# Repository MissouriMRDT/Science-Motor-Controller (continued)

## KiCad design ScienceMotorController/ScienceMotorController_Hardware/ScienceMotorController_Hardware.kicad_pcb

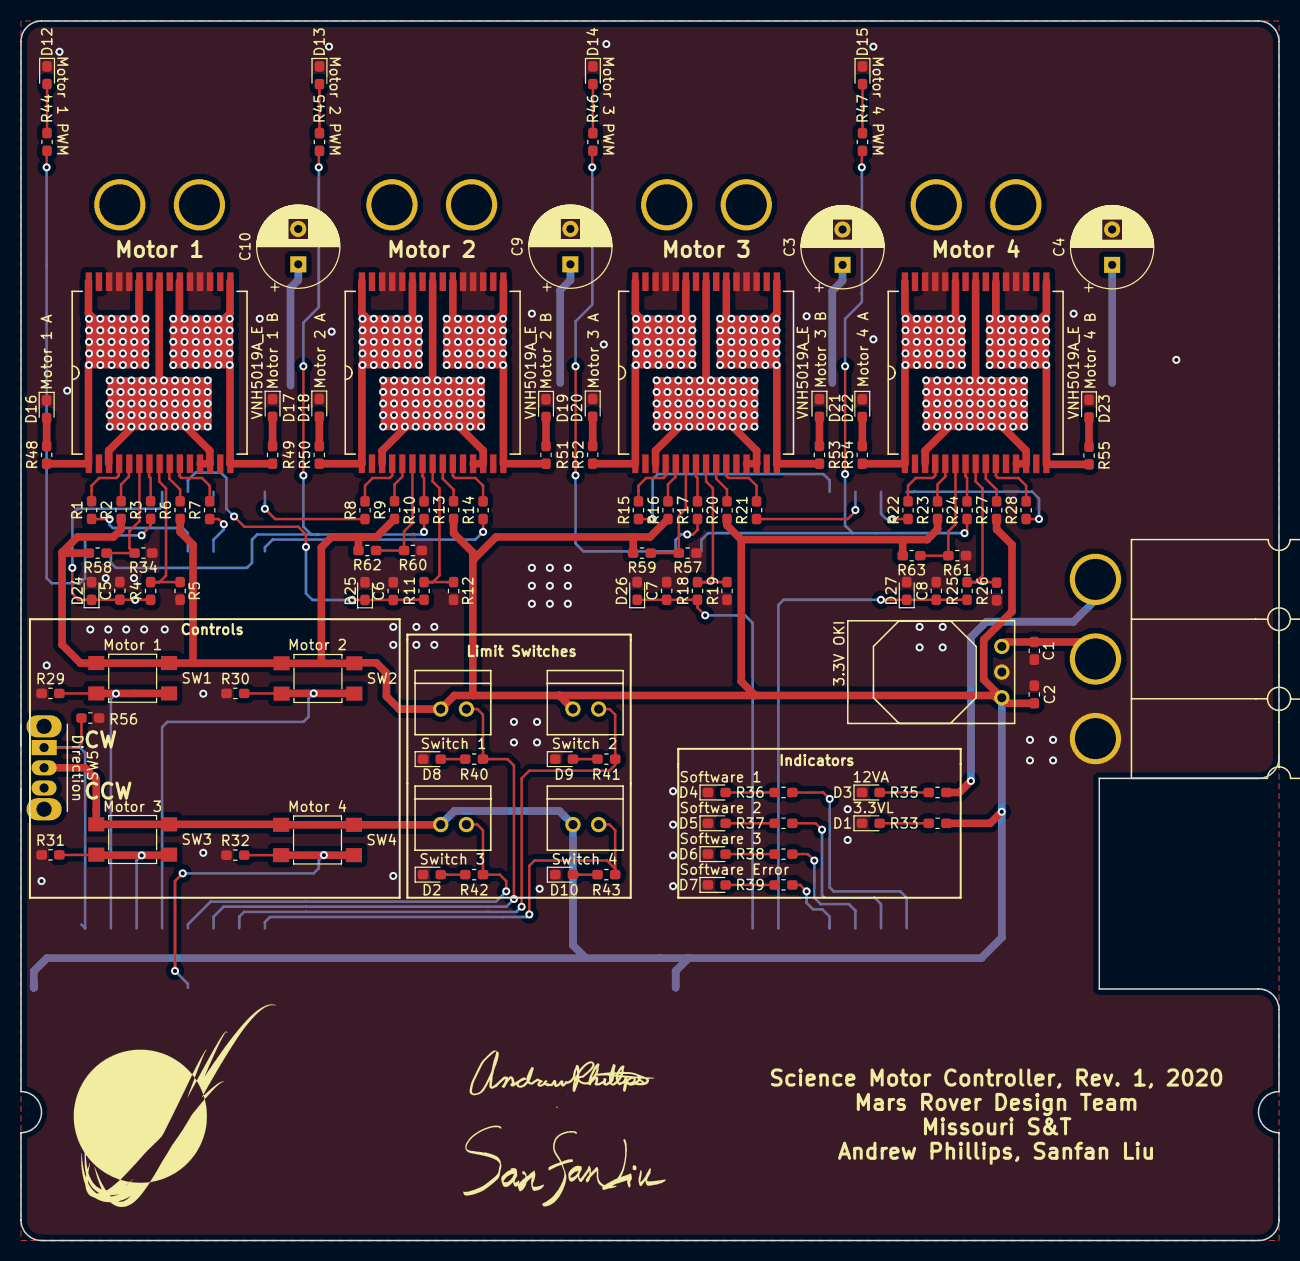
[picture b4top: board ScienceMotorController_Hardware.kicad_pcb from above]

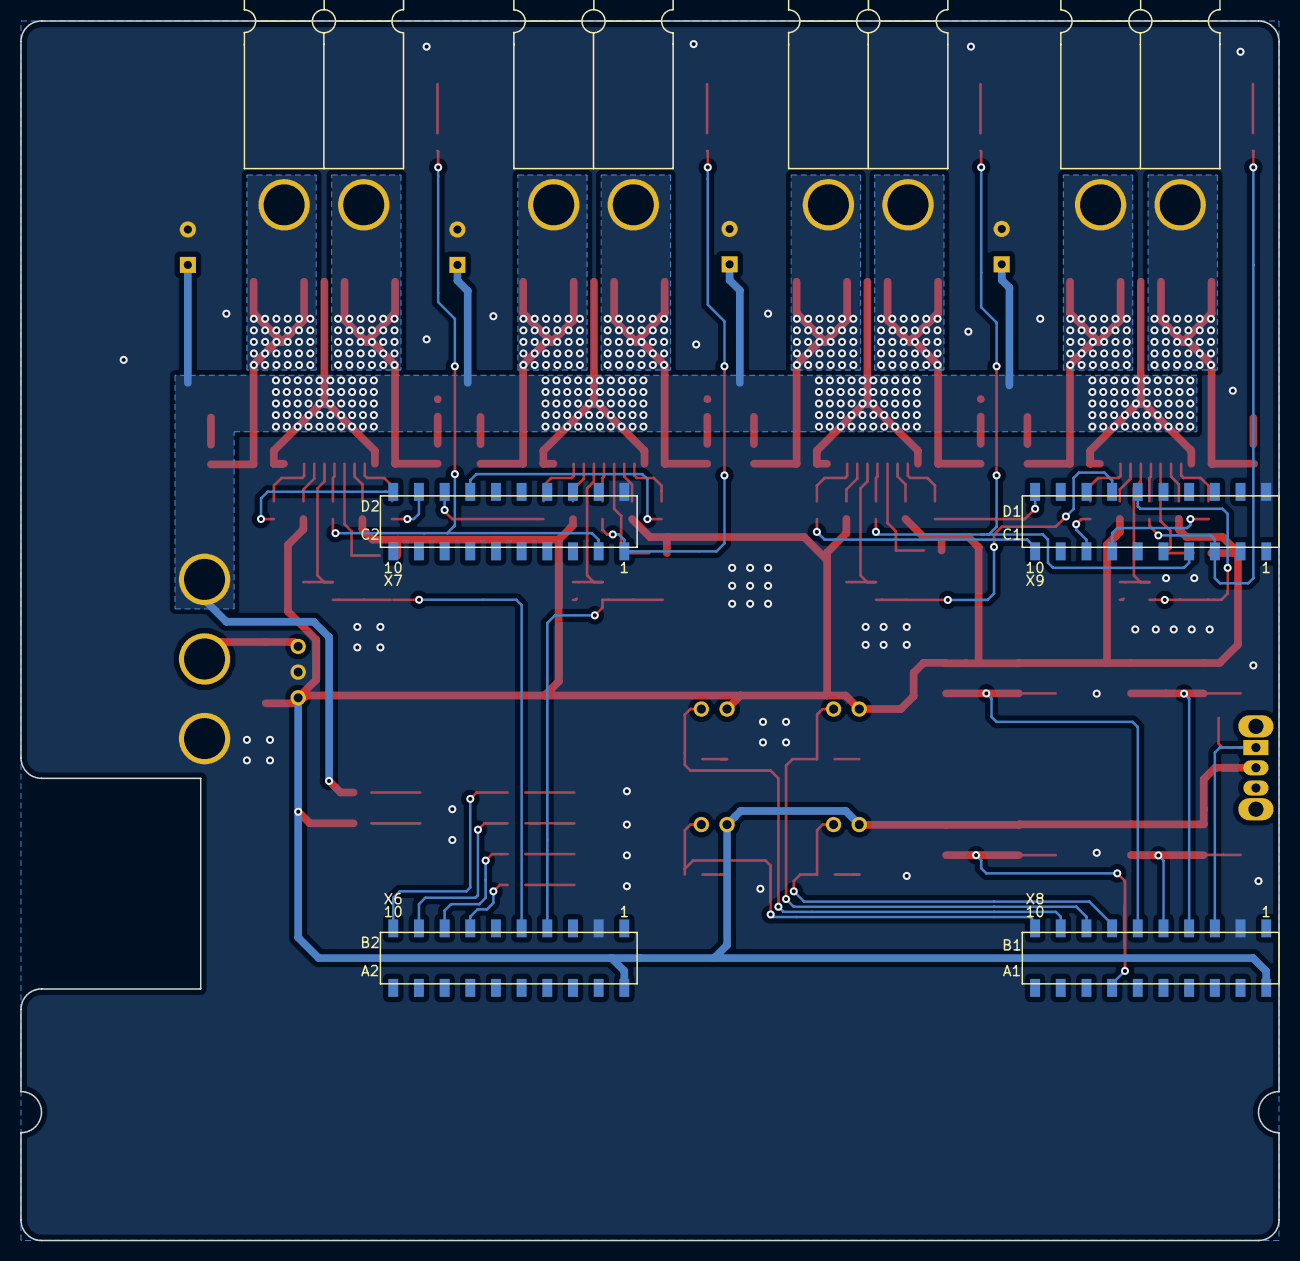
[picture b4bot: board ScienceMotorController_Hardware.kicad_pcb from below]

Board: 2 copper layers, 124.5 x 120.7 mm, 119 parts (4 on the bottom side), 91 nets.

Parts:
C1, C2: 10uF; C_0603_1608Metric_Pad1.05x0.95mm_HandSolder
C3, C4, C9, C10: 470 uF; CP_Radial_D8.0mm_P3.50mm
C5, C6, C7, C8: 33nF; C_0603_1608Metric_Pad1.05x0.95mm_HandSolder
Conn1: AndersonPP; Anderson_3_Horizontal_Side_by_Side
Conn2, Conn3, Conn4, Conn5: AndersonPP; Anderson_2_Horizontal_Side_by_Side
Conn6, Conn7, Conn8, Conn9: Molex_SL_02; MOLEX_SL_02_Vertical
D1: 3.3V_LED; LED_0603_1608Metric_Pad1.05x0.95mm_HandSolder
D2: LS_3_LED; LED_0603_1608Metric_Pad1.05x0.95mm_HandSolder
D3: 12VA_LED; LED_0603_1608Metric_Pad1.05x0.95mm_HandSolder
D4: SW_IND_1_LED; LED_0603_1608Metric_Pad1.05x0.95mm_HandSolder
D5: SW_IND_2_LED; LED_0603_1608Metric_Pad1.05x0.95mm_HandSolder
D6: SW_IND_3_LED; LED_0603_1608Metric_Pad1.05x0.95mm_HandSolder
D7: SW_ERR_LED; LED_0603_1608Metric_Pad1.05x0.95mm_HandSolder
D8: LS_1_LED; LED_0603_1608Metric_Pad1.05x0.95mm_HandSolder
D9: LS_2_LED; LED_0603_1608Metric_Pad1.05x0.95mm_HandSolder
D10: LS_4_LED; LED_0603_1608Metric_Pad1.05x0.95mm_HandSolder
D12: M1_PWM_LED; LED_0603_1608Metric_Pad1.05x0.95mm_HandSolder
D13: M2_PWM_LED; LED_0603_1608Metric_Pad1.05x0.95mm_HandSolder
D14: M3_PWM_LED; LED_0603_1608Metric_Pad1.05x0.95mm_HandSolder
D15: M4_PWM_LED; LED_0603_1608Metric_Pad1.05x0.95mm_HandSolder
D16: M1_OUT_A_LED; LED_0603_1608Metric_Pad1.05x0.95mm_HandSolder
D17: M1_OUT_B_LED; LED_0603_1608Metric_Pad1.05x0.95mm_HandSolder
D18: M2_OUT_A_LED; LED_0603_1608Metric_Pad1.05x0.95mm_HandSolder
D19: M2_OUT_B_LED; LED_0603_1608Metric_Pad1.05x0.95mm_HandSolder
D20: M3_OUT_A_LED; LED_0603_1608Metric_Pad1.05x0.95mm_HandSolder
D21: M3_OUT_B_LED; LED_0603_1608Metric_Pad1.05x0.95mm_HandSolder
D22: M4_OUT_A_LED; LED_0603_1608Metric_Pad1.05x0.95mm_HandSolder
D23: M4_OUT_B_LED; LED_0603_1608Metric_Pad1.05x0.95mm_HandSolder
D24, D25, D26, D27: 3.3 Zener; D_0603_1608Metric_Pad1.05x0.95mm_HandSolder
R1, R2, R3, R6, R7, R8, R9, R10, R13, R14, R15, R16, R17, R20, R21, R22, R23, R24, R27, R28, R48, R49, R50, R51, R52, R53, R54, R55: 1K; R_0603_1608Metric_Pad1.05x0.95mm_HandSolder
R4, R11, R18, R25, R29, R30, R31, R32, R56: 10K; R_0603_1608Metric_Pad1.05x0.95mm_HandSolder
R5, R12, R19, R26, R35: 1.5K; R_0603_1608Metric_Pad1.05x0.95mm_HandSolder
R33: 500; R_0603_1608Metric_Pad1.05x0.95mm_HandSolder
R34, R57, R58, R59, R60, R61, R62, R63: 0; R_0603_1608Metric_Pad1.05x0.95mm_HandSolder
R36, R37, R38, R39, R40, R41, R42, R43, R44, R45, R46, R47: 330; R_0603_1608Metric_Pad1.05x0.95mm_HandSolder
SW1, SW2, SW3, SW4: SW_Push; SW_SPST_TL3305A
SW5: SW_SPDT; SW_CuK_OS102011MA1QN1_SPDT_Angled
U1: TM4C129E_Launchpad; TM4C129E_Launchpad_FULL_SMD_BOTTOM
U2: 3.3V OKI; OKI_Horizontal
U4, U5, U6, U7: VNH5019A_E; MultiPowerSO_30

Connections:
+3V3: C2.1, Conn6.1, Conn7.1, Conn8.1, Conn9.1, R2.1, R6.1, R9.1, R13.1, R16.1, R20.1, R23.1, R27.1, R33.1, R58.2, R59.2, R62.2, R63.2, SW1.1, SW2.1, SW3.1, SW4.1, SW5.2, U1.+3V3, U1.+3V3', U2.3
+12L: C1.1, Conn1.2, U2.1
+12VA: C3.1, C4.1, C9.1, C10.1, Conn1.3, R35.1, U4.3, U4.12, U4.13, U4.23, U4.32, U5.3, U5.12, U5.13, U5.23, U5.32, U6.3, U6.12, U6.13, U6.23, U6.32, U7.3, U7.12, U7.13, U7.23, U7.32
GND: C1.2, C2.2, C3.2, C4.2, C5.2, C6.2, C7.2, C8.2, C9.2, C10.2, Conn1.1, D1.1, D2.1, D3.1, D4.1, D5.1, D6.1, D7.1, D8.1, D9.1, D10.1, D12.1, D13.1, D14.1, D15.1, D16.1, D17.1, D18.1, D19.1, D20.1, D21.1, D22.1, D23.1, D24.2, D25.2, D26.2, D27.2, R5.2, R12.2, R19.2, R26.2, R29.1, R30.1, R31.1, R32.1, R34.1, R56.1, R57.1, R60.1, R61.1, U1.GND, U2.2, U4.18, U4.19, U4.20, U4.26, U4.27, U4.28, U5.18, U5.19, U5.20, U5.26, U5.27, U5.28, U6.18, U6.19, U6.20, U6.26, U6.27, U6.28, U7.18, U7.19, U7.20, U7.26, U7.27, U7.28
LS_1: Conn6.2, R40.1, U1.PA6
LS_2: Conn7.2, R41.1, U1.PM4
LS_3: Conn8.2, R42.1, U1.PD7
LS_4: Conn9.2, R43.1, U1.PM5
M1_CS: C5.1, D24.1, R4.1, U1.PD1
M1_IN_A: R1.1, U1.PL0
M1_IN_B: R7.1, U1.PL1
M1_OUT_A: Conn2.1, R48.1, U4.1, U4.25, U4.30, U4.31
M1_OUT_B: Conn2.2, R49.1, U4.15, U4.16, U4.21, U4.33
M1_PWM: R3.1, R44.2, U1.PF3
M2_CS: C6.1, D25.1, R11.1, U1.PD0
M2_IN_A: R8.1, U1.PP2
M2_IN_B: R14.1, U1.PL3
M2_OUT_A: Conn3.1, R50.1, U5.1, U5.25, U5.30, U5.31
M2_OUT_B: Conn3.2, R51.1, U5.15, U5.16, U5.21, U5.33
M2_PWM: R10.1, R45.2, U1.PG0
M3_CS: C7.1, D26.1, R18.1, U1.PB5
M3_IN_A: R15.1, U1.PQ3
M3_IN_B: R21.1, U1.PP3
M3_OUT_A: Conn4.1, R52.1, U6.1, U6.25, U6.30, U6.31
M3_OUT_B: Conn4.2, R53.1, U6.15, U6.16, U6.21, U6.33
M3_PWM: R17.1, R46.2, U1.PG1
M4_CS: C8.1, D27.1, R25.1, U1.PK0
M4_IN_A: R22.1, U1.PQ1
M4_IN_B: R28.1, U1.PM6
M4_OUT_A: Conn5.1, R54.1, U7.1, U7.25, U7.30, U7.31
M4_OUT_B: Conn5.2, R55.1, U7.15, U7.16, U7.21, U7.33
M4_PWM: R24.1, R47.2, U1.PK4
MSW_1: R29.2, SW1.2, U1.PE1
MSW_2: R30.2, SW2.2, U1.PE3
MSW_3: R31.2, SW3.2, U1.PE2
MSW_4: R32.2, SW4.2, U1.PD3
MSW_5: R56.2, SW5.1, U1.PE0
unnamed: D1.2, R33.2
unnamed: D2.2, R42.2
unnamed: D3.2, R35.2
unnamed: D4.2, R36.2
unnamed: D5.2, R37.2
unnamed: D6.2, R38.2
unnamed: D7.2, R39.2
unnamed: D8.2, R40.2
unnamed: D9.2, R41.2
unnamed: D10.2, R43.2
unnamed: D12.2, R44.1
unnamed: D13.2, R45.1
unnamed: D14.2, R46.1
unnamed: D15.2, R47.1
unnamed: D16.2, R48.2
unnamed: D17.2, R49.2
unnamed: D18.2, R50.2
unnamed: D19.2, R51.2
unnamed: D20.2, R52.2
unnamed: D21.2, R53.2
unnamed: D22.2, R54.2
unnamed: D23.2, R55.2
unnamed: R1.2, U4.4
unnamed: R2.2, U4.5
unnamed: R3.2, U4.7
unnamed: R4.2, R5.1, U4.8
unnamed: R6.2, U4.9
unnamed: R7.2, U4.10
unnamed: R8.2, U5.4
unnamed: R9.2, U5.5
unnamed: R10.2, U5.7
unnamed: R11.2, R12.1, U5.8
unnamed: R13.2, U5.9
unnamed: R14.2, U5.10
unnamed: R15.2, U6.4
unnamed: R16.2, U6.5
unnamed: R17.2, U6.7
unnamed: R18.2, R19.1, U6.8
unnamed: R20.2, U6.9
unnamed: R21.2, U6.10
unnamed: R22.2, U7.4
unnamed: R23.2, U7.5
unnamed: R24.2, U7.7
unnamed: R25.2, R26.1, U7.8
unnamed: R27.2, U7.9
unnamed: R28.2, U7.10
unnamed: R34.2, R58.1, U4.6
unnamed: R57.2, R59.1, U6.6
unnamed: R60.2, R62.1, U5.6
unnamed: R61.2, R63.1, U7.6
SW_ERR: R39.1, U1.PK2
SW_IND_1: R36.1, U1.PA5
SW_IND_2: R37.1, U1.PA4
SW_IND_3: R38.1, U1.PK3

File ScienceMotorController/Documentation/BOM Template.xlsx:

Id | Designator | Package | Quantity | Designation | Item Name | Part Number | Vendor | Cost Per Item | Cost | URL | Comments
1 | U5,U4,U6,U7 | MultiPowerSO_30 | 4 | VNH5019A_E | VNH5019ATR-E | 497-13073-1-ND | Digikey | 7.91 | 31.64 | https://www.digikey.com/product-detail/en/stmicroelectronics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 |  |  |  | Total Cost
2 | R43,R39,R40,R41,R44,R45,R46,R47,R42 | R_0603_1608Metric_Pad1.05x0.95mm_HandSolder | 9 | 330 | CRCW0603330RJNEA | 59M6805 | Newark | 2E-3 | 1.8000000000000002E-2 | https://www.newark.com/vishay/crcw0603330rjnea/res-thick-fil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 |  |  |  | 19.779
3 | R36,R37,R38,R29,R30,R31,R32,R33,R56 | R_0603_1608Metric_Pad1.05x0.95mm_HandSolder | 9 | 500 | CRCW0603510RJNEA | 59M6823 | Newark | 4.0000000000000001E-3 | 3.6000000000000004E-2 | https://www.newark.com/vishay/crcw0603510rjnea/res-thick-fil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
4 | C8,C5,C6,C7 | C_0603_1608Metric_Pad1.05x0.95mm_HandSolder | 4 | 33nF | 311-4001-1 | 311-4001-1-ND | Digikey | 0.11 | 0.44 | https://www.digikey.com/product-detail/en/yageo/CC0603JRX7R8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
5 | C1,C2 | C_0603_1608Metric_Pad1.05x0.95mm_HandSolder | 2 | 10uF | 1608-1357-1 | 1608-1357-1-ND | Digikey | 0.35 | 0.7 | https://www.digikey.com/product-detail/en/knowles-syfer/0603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
6 | Conn1 | Anderson_3_Horizontal_Side_by_Side | 1 | AndersonPP |  |  |  |  | 0
7 | Conn2,Conn3,Conn4,Conn5 | Anderson_2_Horizontal_Side_by_Side | 4 | AndersonPP |  |  |  |  | 0
8 | D1 | LED_0603_1608Metric_Pad1.05x0.95mm_HandSolder | 1 | 3.3V_LED | SML-LX0603GW-TR | 75K1440 | Newark | 0.24299999999999999 | 0.24299999999999999 | https://www.newark.com/lumex/sml-lx0603gw-tr/led-green-0-8mm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
9 | D3 | LED_0603_1608Metric_Pad1.05x0.95mm_HandSolder | 1 | 12VA_LED | SML-LX0603GW-TR | 75K1440 | Newark | 0.24299999999999999 | 0.24299999999999999 | https://www.newark.com/lumex/sml-lx0603gw-tr/led-green-0-8mm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
10 | D4 | LED_0603_1608Metric_Pad1.05x0.95mm_HandSolder | 1 | SW_IND_1_LED | SML-LX0603USBW-TR | 70M9169 | Newark | 1.03 | 1.03 | https://www.newark.com/lumex/sml-lx0603usbw-tr/led-blue-0-8m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
11 | D5 | LED_0603_1608Metric_Pad1.05x0.95mm_HandSolder | 1 | SW_IND_2_LED | SML-LX0603USBW-TR | 70M9169 | Newark | 1.03 | 1.03 | https://www.newark.com/lumex/sml-lx0603usbw-tr/led-blue-0-8m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
12 | D6 | LED_0603_1608Metric_Pad1.05x0.95mm_HandSolder | 1 | SW_IND_3_LED | SML-LX0603USBW-TR | 70M9169 | Newark | 1.03 | 1.03 | https://www.newark.com/lumex/sml-lx0603usbw-tr/led-blue-0-8m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
13 | D7 | LED_0603_1608Metric_Pad1.05x0.95mm_HandSolder | 1 | SW_ERR_LED | SML-LX0603SIW-TR | 09J9435 | Newark | 0.62 | 0.62 | https://www.newark.com/lumex/sml-lx0603siw-tr/led-red-0-8mm-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
14 | D8 | LED_0603_1608Metric_Pad1.05x0.95mm_HandSolder | 1 | LS_1_LED | SML-LX0603SYW-TR | 28M9280 | Newark | 0.107 | 0.107 | https://www.newark.com/lumex/sml-lx0603syw-tr/led-yellow-0-8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
15 | D9 | LED_0603_1608Metric_Pad1.05x0.95mm_HandSolder | 1 | LS_2_LED | SML-LX0603SYW-TR | 28M9280 | Newark | 0.107 | 0.107 | https://www.newark.com/lumex/sml-lx0603syw-tr/led-yellow-0-8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
14 | D2 | LED_0603_1608Metric_Pad1.05x0.95mm_HandSolder | 1 | LS_1_LED | SML-LX0603SYW-TR | 28M9280 | Newark | 0.107 | 0.107 | https://www.newark.com/lumex/sml-lx0603syw-tr/led-yellow-0-8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
15 | D10 | LED_0603_1608Metric_Pad1.05x0.95mm_HandSolder | 1 | LS_2_LED | SML-LX0603SYW-TR | 28M9280 | Newark | 0.107 | 0.107 | https://www.newark.com/lumex/sml-lx0603syw-tr/led-yellow-0-8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
16 | D12 | LED_0603_1608Metric_Pad1.05x0.95mm_HandSolder | 1 | M1_PWM_LED | SML-LX0603SYW-TR | 28M9280 | Newark | 0.107 | 0.107 | https://www.newark.com/lumex/sml-lx0603syw-tr/led-yellow-0-8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
17 | D13 | LED_0603_1608Metric_Pad1.05x0.95mm_HandSolder | 1 | M2_PWM_LED | SML-LX0603SYW-TR | 28M9280 | Newark | 0.107 | 0.107 | https://www.newark.com/lumex/sml-lx0603syw-tr/led-yellow-0-8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
18 | D14 | LED_0603_1608Metric_Pad1.05x0.95mm_HandSolder | 1 | M3_PWM_LED | SML-LX0603SYW-TR | 28M9280 | Newark | 0.107 | 0.107 | https://www.newark.com/lumex/sml-lx0603syw-tr/led-yellow-0-8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
19 | D15 | LED_0603_1608Metric_Pad1.05x0.95mm_HandSolder | 1 | M4_PWM_LED | SML-LX0603SYW-TR | 28M9280 | Newark | 0.107 | 0.107 | https://www.newark.com/lumex/sml-lx0603syw-tr/led-yellow-0-8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
20 | D16 | LED_0603_1608Metric_Pad1.05x0.95mm_HandSolder | 1 | M1_OUT_A_LED | SML-LX0603SOW-TR | 28M9279 | Newark | 0.11700000000000001 | 0.11700000000000001 | https://www.newark.com/lumex/sml-lx0603sow-tr/led-orange-0-8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
21 | D17 | LED_0603_1608Metric_Pad1.05x0.95mm_HandSolder | 1 | M1_OUT_B_LED | SML-LX0603SOW-TR | 28M9279 | Newark | 0.11700000000000001 | 0.11700000000000001 | https://www.newark.com/lumex/sml-lx0603sow-tr/led-orange-0-8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
22 | D18 | LED_0603_1608Metric_Pad1.05x0.95mm_HandSolder | 1 | M2_OUT_A_LED | SML-LX0603SOW-TR | 28M9279 | Newark | 0.11700000000000001 | 0.11700000000000001 | https://www.newark.com/lumex/sml-lx0603sow-tr/led-orange-0-8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
23 | D19 | LED_0603_1608Metric_Pad1.05x0.95mm_HandSolder | 1 | M2_OUT_B_LED | SML-LX0603SOW-TR | 28M9279 | Newark | 0.11700000000000001 | 0.11700000000000001 | https://www.newark.com/lumex/sml-lx0603sow-tr/led-orange-0-8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
24 | D20 | LED_0603_1608Metric_Pad1.05x0.95mm_HandSolder | 1 | M3_OUT_A_LED | SML-LX0603SOW-TR | 28M9279 | Newark | 0.11700000000000001 | 0.11700000000000001 | https://www.newark.com/lumex/sml-lx0603sow-tr/led-orange-0-8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
25 | D21 | LED_0603_1608Metric_Pad1.05x0.95mm_HandSolder | 1 | M3_OUT_B_LED | SML-LX0603SOW-TR | 28M9279 | Newark | 0.11700000000000001 | 0.11700000000000001 | https://www.newark.com/lumex/sml-lx0603sow-tr/led-orange-0-8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
26 | D22 | LED_0603_1608Metric_Pad1.05x0.95mm_HandSolder | 1 | M4_OUT_A_LED | SML-LX0603SOW-TR | 28M9279 | Newark | 0.11700000000000001 | 0.11700000000000001 | https://www.newark.com/lumex/sml-lx0603sow-tr/led-orange-0-8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
27 | D23 | LED_0603_1608Metric_Pad1.05x0.95mm_HandSolder | 1 | M4_OUT_B_LED | SML-LX0603SOW-TR | 28M9279 | Newark | 0.11700000000000001 | 0.11700000000000001 | https://www.newark.com/lumex/sml-lx0603sow-tr/led-orange-0-8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
28 | R1,R2,R3,R6,R7,R8,R9,R10,R13,R14,R15,R16,R17,R20,R21,R22,R23,R24,R27,R28 | R_0603_1608Metric_Pad1.05x0.95mm_HandSolder | 20 | 1K | ESR03EZPJ102 | 59AC6943 | Newark | 0.1 | 2 | https://www.newark.com/rohm/esr03ezpj102/res-1k-5-0603-thick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
29 | R4,R11,R18,R25 | R_0603_1608Metric_Pad1.05x0.95mm_HandSolder | 4 | 10K |  |  |  |  | 0
30 | R5,R12,R19,R26,R35,R48,R49,R50,R51,R52,R53,R54,R55 | R_0603_1608Metric_Pad1.05x0.95mm_HandSolder | 13 | 1.5K |  |  |  |  | 0
31 | SW1,SW2,SW3,SW4 | SW_SPST_TL3305A | 4 | SW_Push |  |  |  |  | 0
32 | U2 | OKI_Horizontal | 1 | 3.3V OKI | OKI-78SR-3 | 58T9850 | Newark | 4.57 | 4.57 | https://www.newark.com/murata-power-solutions/oki-78sr-3-3-1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
33 | Conn8,Conn9,Conn6,Conn7 | MOLEX_SL_02_Vertical | 4 | Molex_SL_02 | 70543-0001 | 59H2645 | Newark | 0.745 | 2.98 | https://www.newark.com/molex/70543-0001/connector-header-2po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
34 | D24,D25,D26,D27 | D_0603_1608Metric_Pad1.05x0.95mm_HandSolder | 4 | 3.3 |  |  |  |  | 0
35 | U1 | TM4C129E_Launchpad_FULL_SMD_BOTTOM | 1 | TM4C129E_Launchpad |  |  |  |  | 0
36 | C3,C4,C9,C10 | CP_Radial_D8.0mm_P3.50mm | 4 | 470 uF |  |  |  |  | 0
37 | SW5 | SW_CuK_OS102011MA1QN1_SPDT_Angled | 1 | SW_SPDT |  |  |  |  | 0

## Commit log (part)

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2019-10-05 Started Schematic
2019-10-08 Added Indicators and Pins
2019-10-08 Controls Added and Schematic Organized
2019-10-08 Updated Schematic Labels and Organization
2019-10-08 (Most) Footprints Assigned
2019-10-08 Footprints and Pins Finished Schematic
2019-10-10 Basic board organization
2019-10-11 Went Overboard on Traces
2019-10-11 Almost All Traces, Ground and 3V3 Polygons
2019-10-12 Finally Added Silkscreens
2019-10-12 Routed All Traces
2019-10-12 Fixed Silkscreen
2019-10-13 PDR Advice
    Removed 2 limit switches & relocated LS LEDs, added direction switch. Also relocated LS, Control, and Indicator blocks and revamped pin assignments to optimize traces.
2019-10-13 Finished Traces
2019-11-16 Added Pin Mapping
2019-12-13 Moving to Rev1 PRR
2019-12-13 Updated Directory Format
2019-12-13 PRR Complete
2019-12-14 BOM Finished
2019-12-14 Step files, updated pin layout, cleaned schematic
2020-09-12 New Repo
2020-09-25 Added Power Sheet
2020-09-25 Added 3.3v buck, created tiva hierachal sheet
2020-09-25 Placed Tiva headers, took note of which pins were PWM
2020-09-25 Added 12VA anderson
2020-10-05 power indicators
2020-10-05 created motors hierarchal sheet, added VNH IC
2020-10-07 Set up VNH IC's
2020-10-07 limit switch indicators
2020-10-07 Flagged Tiva
2020-10-09 changed everything to actuation, added schottky diode, added A/B flags to tiva
2020-10-10 added ferrite beads
2020-10-16 schematic review
2020-10-16 made some more hierarchal changes
2020-10-28 fixed hierarchical
2020-10-31 Fixed 3.3V, added encoders
2020-11-10 added logic line
2020-11-12 annotated
2020-11-12 assigned most of the footprints
2020-11-12 finished assigning footprints, generated pcbnew
2020-11-13 began placing footprints on layout
2020-11-13 more component placing, added ground plane
2020-11-14 added traces for first vnh
2020-11-14 layout work
2020-11-14 more layout work
2020-11-15 finished arranging components
2020-11-15 running traces
2020-11-15 routed more traces
2020-11-15 finished routing traces
2020-11-25 added oki and began rerouting traces
2020-11-26 rerouted traces
2020-11-26 added silkscreens
2020-11-26 added bom
2020-11-26 Added Gerbs
2020-11-26 created step files
2020-11-30 cleaned up vias, widened planes, grounded more areas
2020-12-02 fixed that one trace
2020-12-02 one stray trace
2020-12-02 Fixed Gerbs and Step files
2020-12-02 Fixed BOM mistakes
2021-10-10 schematic meeting review
2021-10-10 Created Branch
2021-11-01 Schematic changes: Added 5V converter and Servos
    Schematic:
    -Added a 5V converter to the power section, connected to Power
    -Added Servos in their own section, altered TIVA to add servo connections
2021-11-30 Finished Schematic
    -Changed Motor Controller Chips
    -Removed 2 Pumps
    -Removed 2 Limit Switches
    -Added 2 Absolute Encoders
    -Added 3 Solenoid Valves
    -Created Schematic Symbol and Footprint for Mosfet (footprint may need to be altered later)
2021-11-30 Netlist Generated
    Generated the netlist for the schematic
2021-12-02 Updated Power
2021-12-02 Added Clock Circuit
2021-12-02 Created PCB and Put Close Components Near Each other
2021-12-03 Edge cuts, GND plane, a little more organized
2021-12-04 Worked on patterns for SolValve, LimSwitch, OKIs, and Clock for PCB
2021-12-04 Added 4 More Limit Switches
2021-12-04 Reassigned Encoder Pins
2021-12-04 Put New LimSwitch compoments next to eachother in PCB layout
2021-12-04 Bunch more traces, slightly fixed some schematic issues
    - LEDs on the solenoid valves were incorrectly labeled as "green".
    - The front plane of the board is now +12VA instead of ground
2021-12-04 Put components on the board and added some traces
2021-12-12 added daisy chain ports, updated andersons
2021-12-12 modified: Hardware/ScienceMotorController/ScienceMotorController.kicad_pcb modified: Hardware/ScienceMotorController/ScienceMotorController.kicad_pcb-bak modified: Hardware/ScienceMotorController/Sci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
2021-12-12 created moco circuits
    Use the GND pin 25 on a 5mil grid with the entire circuit selected to move around
2021-12-12 added components to layout
2021-12-12 organized components to be more space efficient
2021-12-13 changed on oki to 5V actuation for servos, began making solenoid circuits
2021-12-13 more connections, components, and plane changes
2021-12-14 connected servo, sw, solenoid traces. more organization
2021-12-14 more connections made, beginning to connect moco ICs
2021-12-14 resistors on moco chips added.
    Had changed netlist to try a different placement for the motor LEDs, but reverted to original position
2021-12-15 finished moco alignment
2021-12-15 connected 5V and osc. buses to moco ICs. Updated netlist to have pins closer to tiva pins
2021-12-15 continued connecting caps and resistors. Moved around some Tiva pins for the moco ICs
2021-12-15 began reworking moco IC control traces. Will need to rearrange the netlist to reduce complexity of traces
2021-12-15 Completed Board and reviewed with Electrical Leadership
2021-12-16 file cleanup
2021-12-16 removed redundant footprint library
2021-12-17 completed board, ready for ordering
2021-12-27 generated gerbs
2021-12-30 began fixing rescue libraries
    created ScienceMotorController.lib as the new project level library
2021-12-30 removed backup files for the rescue library
2021-12-30 removed redundant libraries
2022-02-22 Layout Ready For Review
2022-02-22 Traces Under Mocos
2022-02-22 Changed Ground Plane for Motor Stalls
2022-02-22 Board Review Changes
2022-02-22 9 Solenoids, Fixed PWM Overlap
2022-02-25 Removed 5V Oki, Moved +12V Passthrough Trace, Added Zener Diodes for Current Sense
2022-03-12 ok but actually this time
2022-03-20 Connected Moco Pads, new Gerbs
2022-09-15 Changed motor controllers to H-bridges
2022-09-15 Modified PWM flags
    Modified PWM flags so orientation matched signal direction, also included whole Project along with generated BOM
2022-09-28 Updated H-bridges and LEDs
2022-09-30 Moved LED to motor outputs
2022-09-30 Plot is PDF
2022-10-11 Updated Motor Controllers
    Now has 7 motor controllers. Relabeled flags on MOCOs. Deleted solenoids. Need to add flags to TIVAs.
2022-10-17 Added Servos
2022-10-17 Added Annotations
2022-10-18 Started Layout
    Update H-Bridges. Added Footprints. Started Layout with edge cuts and coopers.
2022-10-19 Started Layout Design
2022-10-25 Organized Layout
2022-10-26 Layout for Encoders, Servos, and Limit Switches
2022-10-29 Attempted an H-Bridge
2022-10-29 Reworked Layout to be better
2022-10-30 Added H-Bridges. Started Traces
2022-10-31 Made traces for servos and encoders
2022-11-02 Rearranged Board. Traced Power and One H-Bridge
2022-11-03 More tracing. Ground is left.
2022-11-03 Finished layout. BOM is left.
2022-11-07 Board Smaller, H-Bridges moved
2022-11-08 Refit Stuff onto Board.
2022-11-09 Added Mounting Holes
2022-11-09 12V plane made. Started Traces.
2022-11-14 Stuff Happened
2022-11-17 Updated to Teensy.
2022-11-17 Added Ethernet. Expanded Board Temporarily
2022-12-10 Updated Schematic and Sorted Footprints
2022-12-18 H-Bridges organized and on board. PCB components sorted.
2022-12-18 Fixed schematic
2022-12-18 Fixed encoder connections
2022-12-19 Organized limit switches
2022-12-19 Wired servo switches
2022-12-19 Finished buttons, servos, and encoders
2022-12-19 Edge cuts + started H Bridges
2022-12-20 Finished H Bridges
2022-12-20 Stitched planes together
2022-12-20 Fixed trace + made STEP file
2022-12-28 Worked on traces
2022-12-28 Finished board
2022-12-28 Generated BOM + Gerbs
2022-12-28 Changed teensy footprint
2022-12-29 Fixed power plane
2023-01-22 remade STEP file
2023-03-08 Schematic created and updated
2023-03-11 Finished schematic and updated footprints
2023-03-13 Layout generated and organized. Still need to draw traces
2023-03-15 H-Bridges made. Rough placement on board done
2023-03-16 H-Bridges traced internally
2023-03-16 Power traces added. Connections within circuits made.
2023-03-16 Traces done. Ground vias left
2023-03-16 Power anderson footprint changed and more GND vias
2023-03-20 Board has been shrunk.
2023-03-20 Added labels
2023-03-20 Moved signature to KiCad libraries
2023-03-20 Made my signature
2023-03-20 Added Signature. Connected capacitor
2023-05-03 Made STEP file
2023-09-06 Removed Outdated files
2023-09-14 Teensy, limit circuit, MOCO
2023-09-19 Added quad encoders, servos, signal
2023-09-22 Boxed all components; edited heater schematic from a 2 pin connector to three pin, including all the previous connections but also adding a 5v supply
2023-09-23 Generated BOM
    Generated and filled out a portion of the BOM (There are two Orange categories currently, since Orange and ORANGE were both listed. Will merge them together next time (Converted the original format t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
2023-09-23 Delete Science_Actuation.csv
    Removed a semi-duplicate Excel file
2023-09-25 Completed BOM
2023-09-26 Fixed Board for Review
    Changed various aspects, such as adding Mounting Holes, replacing 120Ohm resistors for 100Ohm, added footnotes, changed Heater from Comic Sans to default, etc.
2023-09-26 Fixed Remaining things from the schematic review
    Changing schematic size, added flags to Teensy, removed Science Motor Controller
2023-09-28 Changed anderson to logic, edited BOM
2023-10-10 Updated PCB
    Grouped together the various parts of the board
2023-10-12 Updated Science Actuation PCB
    Oriented the board in a better state
2023-10-13 Uploading base template before Traces
    Base template before traces. Still need to change what routes everything will connect to the Teensy
2023-10-15 Added traces and changed the layout of the board
    Some of it is a mess and will probably be revised later
2023-10-18 Temporary state
    Removed things. Added a motor. WIP
2023-10-18 Tried Cleaning Up Board
    Changed layout, added fourth MOCO Breakout
2023-10-19 Added edge cuts
    Added edge cuts
2023-10-19 Fixed mounting hole locations, did ethernet t+/-, still need ground plane
2023-10-21 Updated board
    Made changes to traces, added Conn17 to BOM (Added motor), added MRDT label.
2023-10-21 Added edge cuts and ground plane
2023-10-31 Updated Schematic
    Cleaned up traces and other miscellaneous things
2023-10-31 Fixed errors, edge cuts, gnd planes, and traces
2023-11-05 Updated Rev1 for parts ordering
    Changed 12V and 5V traces, removed servo3, added heater4, updated BOM (may want to doublecheck the BOM), removed SW9, made labels for switches bigger, and hopefully correctly made the GERB
2023-11-09 Final update for Rev1
    Fixed edgecuts, made silkscreen labels cleaner. Regenerated gerb
2024-03-05 Updated Science Actuation schematic (removed some unnecessary components)
2024-03-13 Updating PCB
2024-03-13 Updated Science Actuation again (definitely not finished)
2024-04-02 Updated PCB Board
2024-04-02 Tried making some more changes to the schematic again (resistors, cutting out some unnecessary LEDS, removed connector for MOCOs)
2024-04-04 Fixed alignment, added MOCOs, removed 2 of 7 buttons, remove LEDs on limit switches
2024-04-04 Small alignment changes
2024-04-04 Updated footprints
2024-04-04 Updated PCB components
2024-04-04 Cleaned Schematic, Restarted PCB, Grouped components for each section
2024-04-05 Reposition all components
2024-04-05 Started connecting traces and positioning components of PCB
2024-04-07 Finished schematic and first draft of layout
2024-04-07 Add more caps to VNH and expand 12V plane
2024-04-07 Generate BOM and tune diff pairs
2024-04-07 Generate gerbs
2024-04-08 Reworked Changes to match Arm Mount
    Reworked traces to match Arm mount and proper power plane calculations utilizing empty space
2024-04-08 lots of layout things; got a pretty solid layout for the moco circuits; still needs a decent bit of cleanup, trace routing, via stitching, etc.
2024-04-09 more routing and shtuff
2024-04-09 Review changes and regenerate gerbs
2024-04-09 finishe layout minus labels
2024-04-10 layout finished??
2024-04-10 labels
2024-04-11 Editing BOM
2024-04-11 Updated BoM Spreadsheet
2024-04-11 Add temp and humidity sensors
2024-04-11 Add temp and humidity sensor
2024-04-18 Updated BOM again (hopefully it is finished)
